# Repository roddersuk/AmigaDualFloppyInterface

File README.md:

# AmigaDualFloppyInterface
**Amiga 500 6A Dual Internal Floppy Drive Interface**

***N.B. I have only tested that this board works with an Issue 6A motherboard***

I have recently acquired an Amiga 500 and wanted to expand its capability by adding a Gotek drive but didn't want to lose the internal floppy drive. I soon came across some of the restrictions of the A500 design which basically meant that if you have the Gotek as the primary, bootable drive the internal floppy drive (df1) wouldn't work. I could have course have gone down the external floppy route but I didn't want all that stuff hanging out the back of the Amiga.

So I started this project with these objectives:
- To support two floppy drives internally to the A500
- To be able to switch which one is bootable
- For the second drive to always be available
- Not to require any irreversible change to the A500
- Not to have any connections out to the external drive port

There are a number of issues to overcome to achieve these objectives:
1. All of the needed signals need to be picked up from the motherboard
2. A motor control signal has to be generated for the second drive
3. A drive identification has to be generated for the second drive
4. Some means of switching between the drives needs to be devised

The design was created using KiCad, the project files are in the KiCad folder. Production ready files are provided in the KiCad/Gerber folder and PDF versions of the schematic, PCB and BOM are provided in the Docs folder.

For more information see the User Guide in the Docs folder.

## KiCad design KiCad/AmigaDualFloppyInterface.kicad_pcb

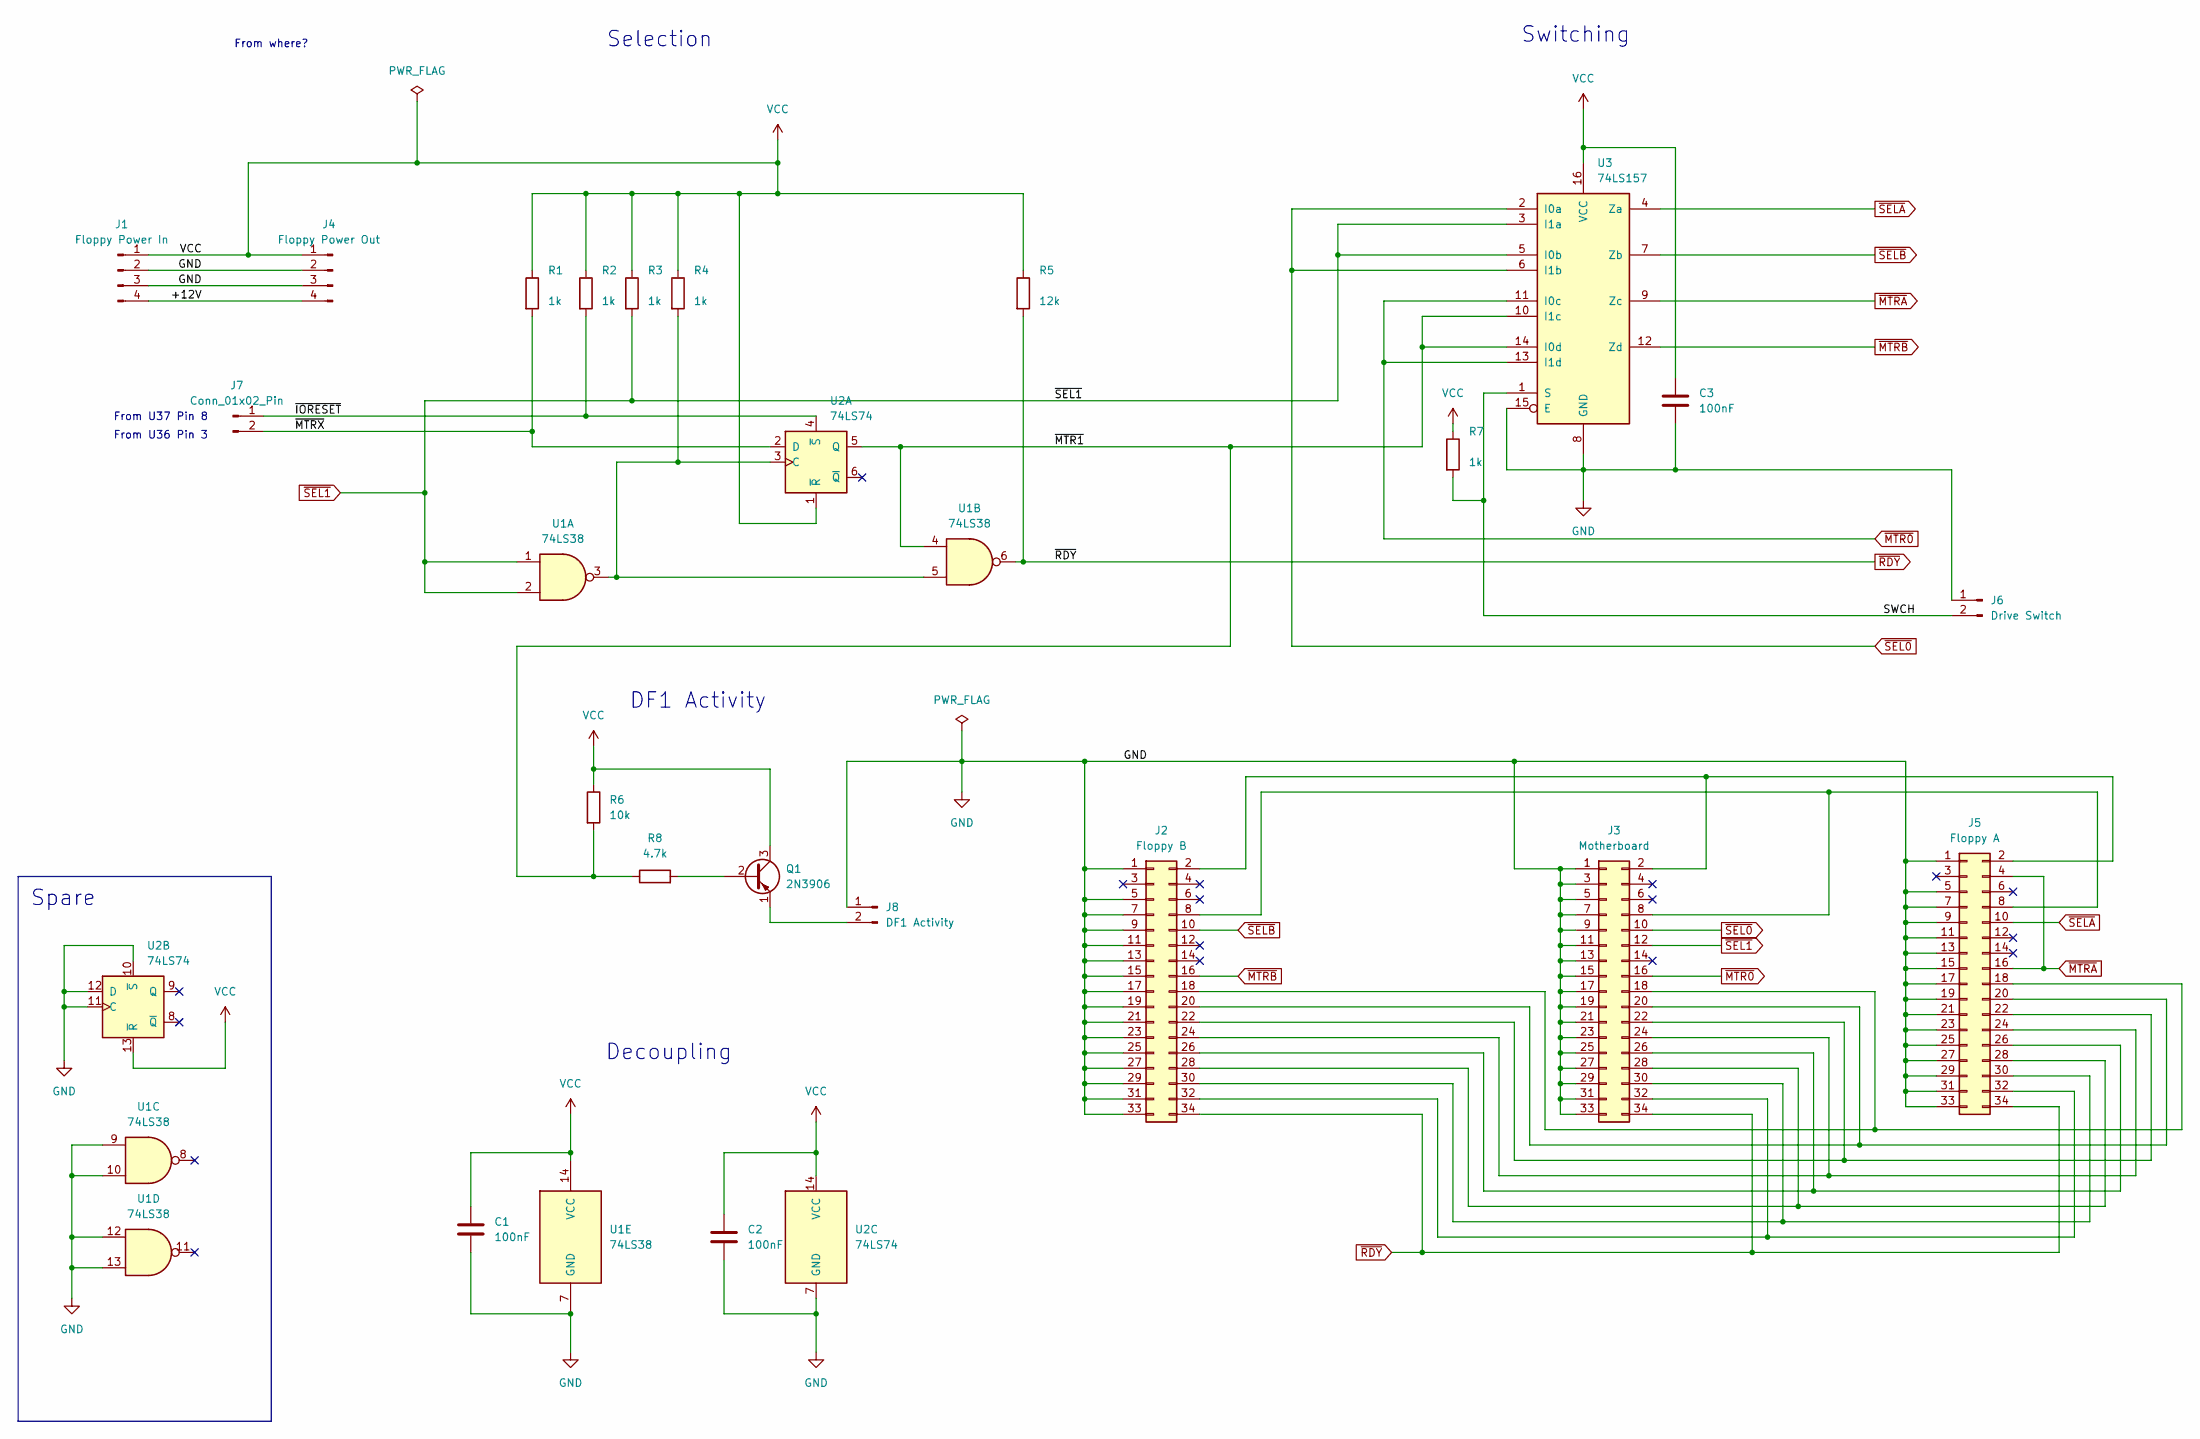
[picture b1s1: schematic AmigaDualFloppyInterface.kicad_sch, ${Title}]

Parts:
C1, C2, C3: 100nF; C_Disc_D4.3mm_W1.9mm_P5.00mm
J1: Floppy Power In; PinSocket_1x04_P2.54mm_Vertical
J2: Floppy B; IDC-Header_2x17_P2.54mm_Vertical
J3: Motherboard; PinSocket_2x17_P2.54mm_Vertical
J4: Floppy Power Out; PinHeader_1x04_P2.54mm_Horizontal
J5: Floppy A; IDC-Header_2x17_P2.54mm_Vertical
J6: Drive Switch; PinHeader_1x02_P2.54mm_Horizontal
J7: Conn_01x02_Pin; PinHeader_1x02_P2.54mm_Horizontal
J8: DF1 Activity; PinHeader_1x02_P2.54mm_Horizontal
Q1: 2N3906; TO-92_Inline
R1, R2, R3, R4, R7: 1k; R_Axial_DIN0207_L6.3mm_D2.5mm_P7.62mm_Horizontal
R5: 12k; R_Axial_DIN0207_L6.3mm_D2.5mm_P7.62mm_Horizontal
R6: 10k; R_Axial_DIN0207_L6.3mm_D2.5mm_P7.62mm_Horizontal
R8: 4.7k; R_Axial_DIN0207_L6.3mm_D2.5mm_P7.62mm_Horizontal
U1: 74LS38; DIP-14_W7.62mm
U2: 74LS74; DIP-14_W7.62mm
U3: 74LS157; DIP-16_W7.62mm

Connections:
/+12V: J1.4, J4.4
/SWCH: J6.2, R7.2, U3.1 (S)
/~IORESET: J7.1, R2.2, U2.4 (~S)
/~MTR1: R6.2, R8.1, U1.4, U2.5 (Q), U3.10 (I1c), U3.14 (I0d)
/~MTRX: J7.2, R1.2, U2.2 (D)
GND: C1.2, C2.2, C3.2, J1.2, J1.3, J2.1, J2.5, J2.7, J2.9, J2.11, J2.13, J2.15, J2.17, J2.19, J2.21, J2.23, J2.25, J2.27, J2.29, J2.31, J2.33, J3.1, J3.3, J3.5, J3.7, J3.9, J3.11, J3.13, J3.15, J3.17, J3.19, J3.21, J3.23, J3.25, J3.27, J3.29, J3.31, J3.33, J4.2, J4.3, J5.1, J5.5, J5.7, J5.9, J5.11, J5.13, J5.15, J5.17, J5.19, J5.21, J5.23, J5.25, J5.27, J5.29, J5.31, J5.33, J6.1, J8.1, U1.7 (GND), U1.9, U1.10, U1.12, U1.13, U2.7 (GND), U2.10 (~S), U2.11 (C), U2.12 (D), U3.8 (GND), U3.15 (E)
unnamed: J2.2, J3.2, J5.2
unnamed: J2.8, J3.8, J5.8
unnamed: J2.18, J3.18, J5.18
unnamed: J2.20, J3.20, J5.20
unnamed: J2.22, J3.22, J5.22
unnamed: J2.24, J3.24, J5.24
unnamed: J2.26, J3.26, J5.26
unnamed: J2.28, J3.28, J5.28
unnamed: J2.30, J3.30, J5.30
unnamed: J2.32, J3.32, J5.32
unnamed: J8.2, Q1.1 (E)
unnamed: Q1.2 (B), R8.2
unnamed: R4.2, U1.3, U1.5, U2.3 (C)
VCC: C1.1, C2.1, C3.1, J1.1, J4.1, Q1.3 (C), R1.1, R2.1, R3.1, R4.1, R5.1, R6.1, R7.1, U1.14 (VCC), U2.1 (~R), U2.13 (~R), U2.14 (VCC), U3.16 (VCC)
~MTR0: J3.16, U3.11 (I0c), U3.13 (I1d)
~MTRA: J5.4, J5.16, U3.9 (Zc)
~MTRB: J2.16, U3.12 (Zd)
~RDY: J2.34, J3.34, J5.34, R5.2, U1.6
~SEL0: J3.10, U3.2 (I0a), U3.6 (I1b)
~SEL1: J3.12, R3.2, U1.1, U1.2, U3.3 (I1a), U3.5 (I0b)
~SELA: J5.10, U3.4 (Za)
~SELB: J2.10, U3.7 (Zb)

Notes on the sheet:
Spare
From where?
DF1 Activity
From U36 Pin 3
Decoupling
Switching
Selection
From U37 Pin 8

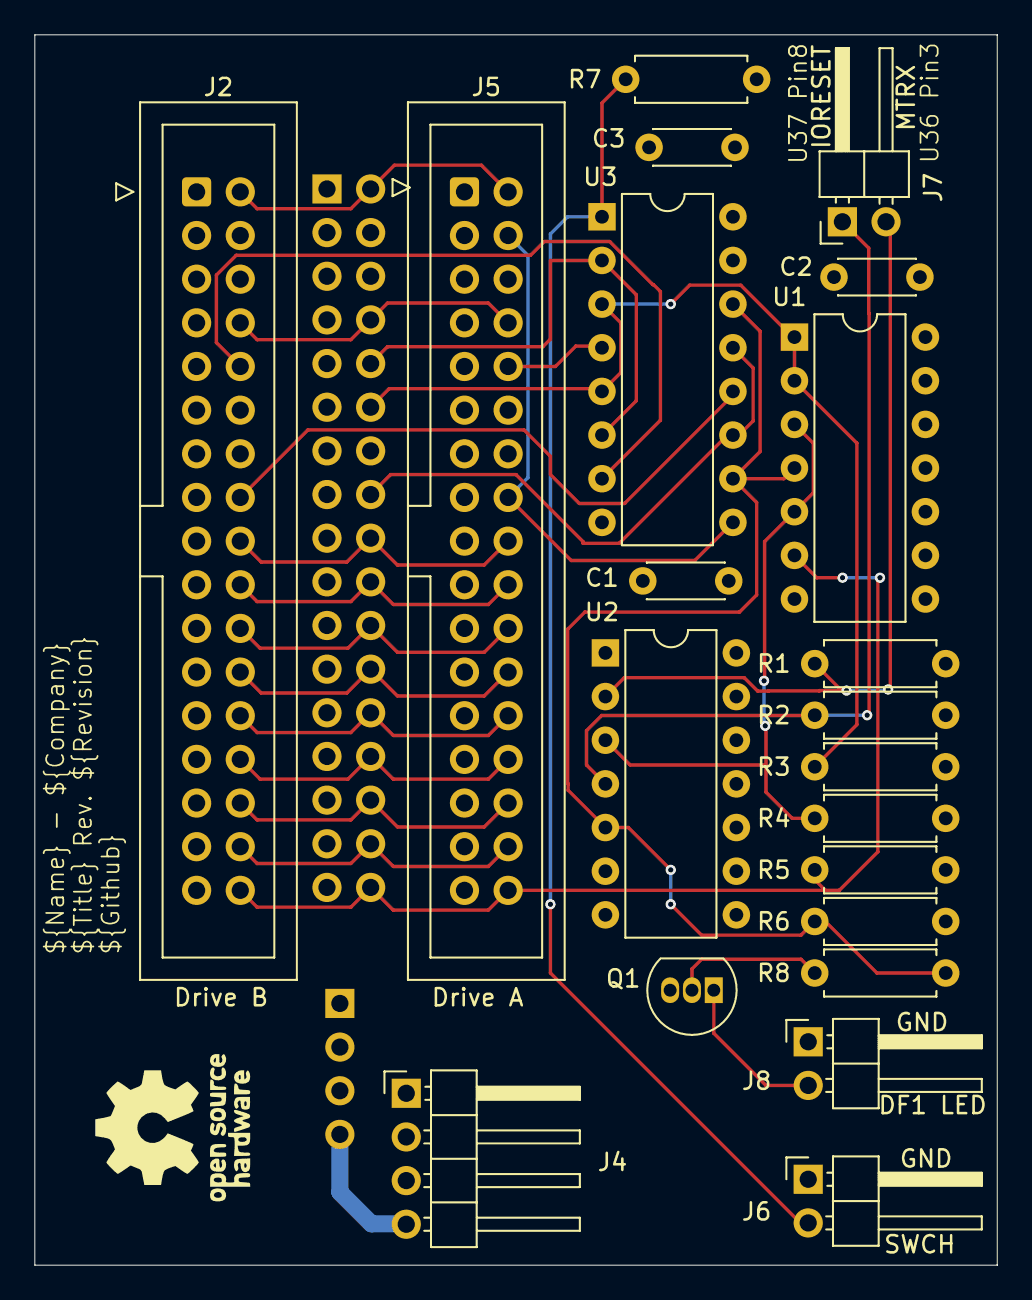
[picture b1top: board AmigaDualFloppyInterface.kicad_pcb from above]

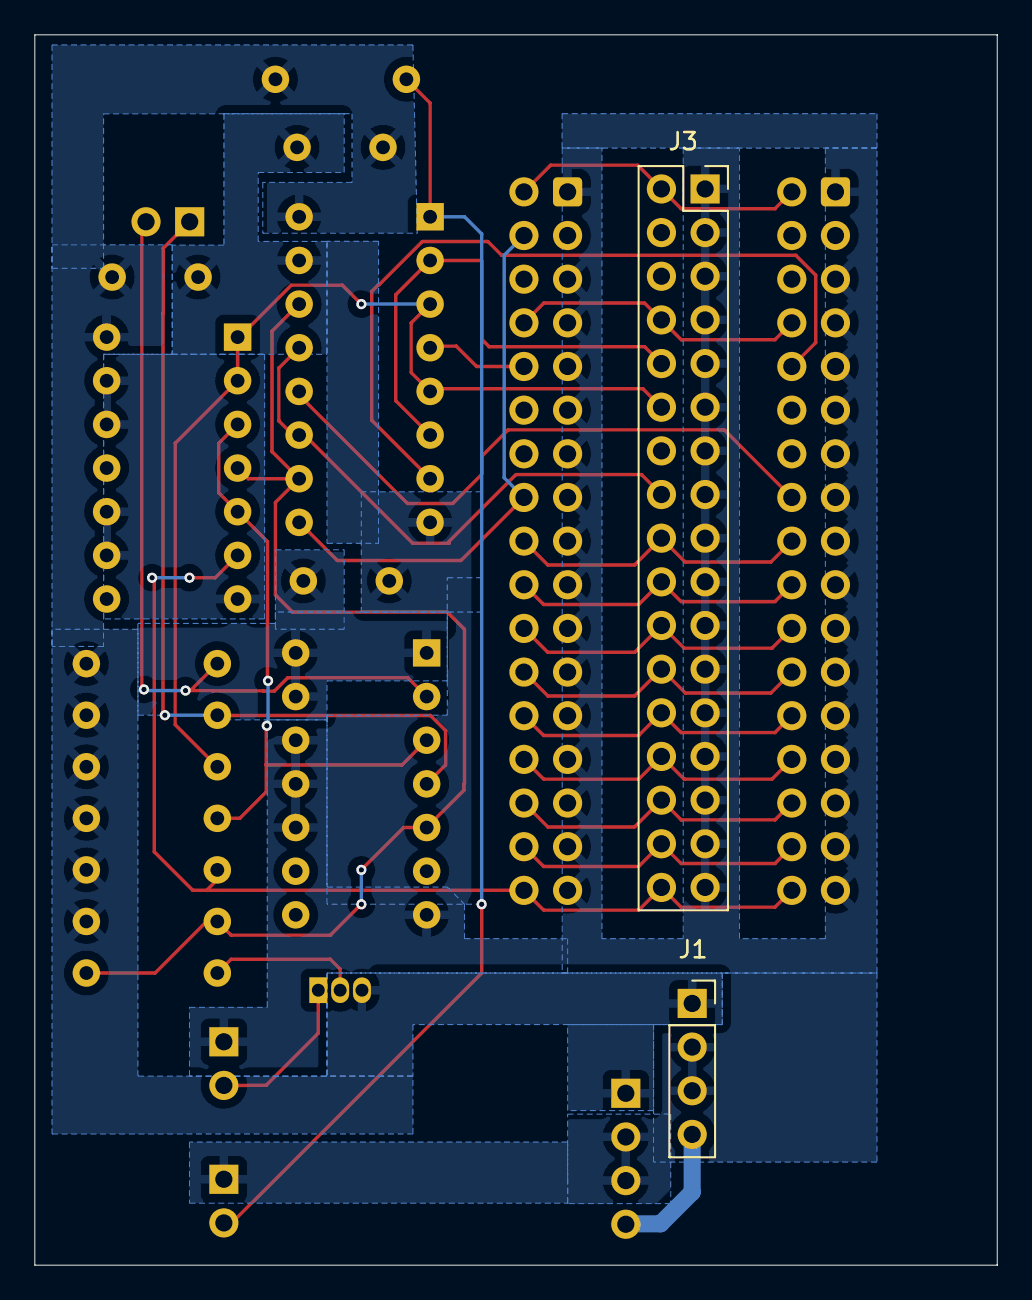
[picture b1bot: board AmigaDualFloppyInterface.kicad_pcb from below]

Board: 2 copper layers, 56.0 x 71.6 mm, 24 parts (2 on the bottom side), 28 nets.

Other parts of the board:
OSHW: LOGO; OSHW_logo

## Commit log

2024-09-09 Update README.md
    First attempt
2024-09-09 Add files via upload
    Initial Upload
2024-09-09 Create x
2024-09-17 Fix project footprint library
2024-09-17 Update footprint library extension
2024-09-23 Add files via upload
    Updated design with separate df1 LED
2024-09-23 Delete KiCad/Gerbers directory
    Old flawed design
2024-10-01 Add files via upload
    Final images addded
2024-10-01 Update README.md
    Ready to go!
2024-10-11 Add files via upload
    Alternative value for R5
2024-10-13 Add files via upload
    Added section on building the board.
2024-10-13 Update README.md
    Added picture of the back of the board
2024-10-13 Update README.md
    Warning that its only tested for 6A
2024-11-12 Rename cern_ohl_p_v2.pdf to LICENSE.pdf
2024-11-13 Delete LICENSE.pdf
    Replaced with LICENSE.txt
2025-09-11 Clarification of MTRX
    Fix for issue "User manual has an error regarding MTRX pin #2"
